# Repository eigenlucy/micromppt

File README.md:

# [micromppt](https://eigenlucy.github.io/projects/micromppt/)

SPV1040 Based 5W MPPT Boost Charger With Autonomous Perturb-and-Observe Set Point Adjustment

Tiny, versatile, high efficiency solar charging, designed with Meshtastic clients in mind

This release has been configured for single cell lipo charging, and includes an [XB3306](https://www.lcsc.com/datasheet/lcsc_datasheet_2106062206_XySemi-XB3306D_C2759992.pdf) lithium battery protection circuit. I have tested this converter with avariety of cell chemistries, as well as supercapacitors, and I will release a more minimal SPV1040 package in the upcoming week with configuration guidelines to for a more general purpose multichemistry solar charging module. [See the project page on my website for more configuration guidelines, panel recommendations, and ordering info (WIP)](https://eigenlucy.github.io/projects/micromppt/).

Built with atopile and KICAD 9. See my [atopile usage guide](/ATO_USAGE.md) for help installing and using atopile

TO DO:
- Split the project into a base micromppt module and a number of input and output projection modules
- Solve Vout divider with assertions, add cutoff and BPC for other chemistries

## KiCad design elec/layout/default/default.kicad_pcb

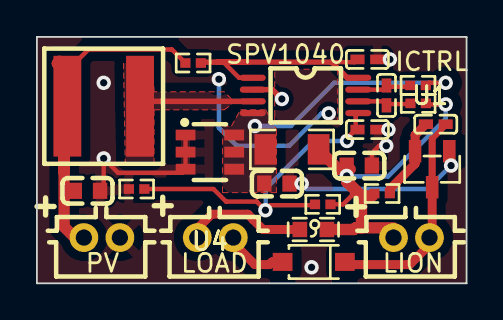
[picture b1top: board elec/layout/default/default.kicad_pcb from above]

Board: 2 copper layers, 23.9 x 13.7 mm, 23 parts (0 on the bottom side), 13 nets.

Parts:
C2: 4.7µF ±10% 16V X5R; C0603
C3: 10µF ±20% 6.3V X5R; C0603
C4: 100nF ±10% 16V X7R; C0402
C5: 1nF ±20% 50V X7R; C0402
C6: 1µF ±10% 25V X5R; C0402
D1: SOD-123F_L2.7-W1.6-LS3.8-RD-1
F1: F0603
R1: 1MΩ ±1% 62.5mW; R0402
R2: 390kΩ ±1% 62.5mW; R0402
R3, R4, R5: 1kΩ ±1% 62.5mW; R0402
R6: 10mΩ ±1% 1W; R1206
U1: TSSOP-8_L4.4-W3.0-P0.65-LS6.4-BL
U2: 100nF ±10% 16V X7R; C0402
U3: IND-SMD_L6.6-W6.4
U4: SOT-23-6_L2.9-W1.6-P0.95-LS2.8-BR
U5: 10µF ±20% 6.3V X5R; C0603
U6: 10kΩ ±1% 62.5mW; R0402
U7, U8, U10: CONN-TH_B2B-PH-K-S
U9: SOT-23-3_L2.9-W1.3-P1.90-LS2.4-BR

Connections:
ICTRL_MINUS: C6.2, R5.1, U1.6
ICTRL_PLUS: C6.1, R4.1, U1.7
LX: U1.3, U3.2
MPP_SET: C4.1, R3.2, U1.1, U1.8
VCTRL: C5.1, R1.2, R2.1, U1.5
VDD: U2.1, U6.1, U9.2
VOUT: C2.1, R4.2, R6.1, U1.4, U4.4, U4.5, U4.6
Vbat: C3.1, F1.1, R1.1, R5.2, R6.2, U6.2, U7.1
Vbatr-GND: D1.1, U2.2, U7.2, U9.3
Vpv: R3.1, U3.1, U5.1, U8.1
_1: F1.2, U10.1
anode: D1.2, U10.2
power_shim-GND: C2.2, C3.2, C4.2, C5.2, R2.2, U1.2, U4.1, U4.2, U4.3, U5.2, U8.2, U9.1

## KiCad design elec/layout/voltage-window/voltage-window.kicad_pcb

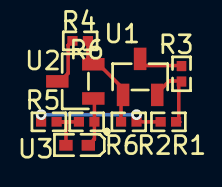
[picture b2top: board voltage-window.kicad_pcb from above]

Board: 2 copper layers, 9 parts (0 on the bottom side), 7 nets.

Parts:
R1, R2, R3, R4, R5, R6: 10kΩ ±1% 62.5mW; R0402-56259e
U1, U2: SOT-23-3_L2.9-W1.3-P1.90-LS2.4-BR-688f29
U3: LED0402-R-RD-049f90

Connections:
A: R3.2, U1.3
K: R2.2, R4.1, U1.1, U2.2
OUT: R6.2, U2.1, U3.2
REF: R1.2, R3.1, U1.2
anode: R5.2, R6.1, U3.1
gnd: R4.2, U2.3
hv: R1.1, R2.1, R5.1

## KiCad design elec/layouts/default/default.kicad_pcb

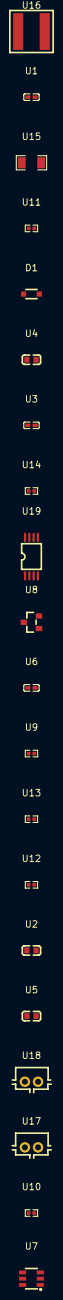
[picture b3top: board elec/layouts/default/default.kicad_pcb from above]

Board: 2 copper layers, 20 parts (0 on the bottom side), 11 nets, no tracks yet.

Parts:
D1: SOD-323F_L1.7-W1.3-LS2.5-R-RD
U1: 1µF ±10% 25V X5R; C0402-b3ef17
U2, U5: 10µF ±20% 6.3V X5R; C0603-bd72f6
U3: 100nF ±10% 16V X7R; C0402-b3ef17
U4: 4.7µF ±10% 10V X5R; C0603-bd72f6
U6: 1nF ±20% 50V X7R; C0402-b3ef17
U7: SOT-23-6_L2.9-W1.6-P0.95-LS2.8-BR
U8: SOT-23_L2.9-W1.3-P1.90-LS2.4-BR
U9: 1MΩ ±1% 62.5mW; R0402-56259e
U10: 330kΩ ±1% 62.5mW; R0402-56259e
U11, U13, U14: 1kΩ ±1% 62.5mW; R0402-56259e
U12: 10kΩ ±1% 62.5mW; R0402-56259e
U15: 10mΩ ±1% 1W; R1206-bdb864
U16: IND-SMD_L6.6-W6.4
U17, U18: CONN-TH_B2B-PH-K-S
U19: TSSOP-8_L4.4-W3.0-P0.65-LS6.4-BL

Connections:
D: D1.1, U8.3, U18.1
G: D1.2, U8.1, U12.1
ICTRL_MINUS: U1.2, U14.1, U19.6
ICTRL_PLUS: U1.1, U13.1, U19.7
LX: U16.2, U19.3
S: U2.1, U8.2, U11.1, U16.1
VCTRL: U6.1, U9.2, U10.1, U19.5
VOUT: U4.1, U13.2, U15.1, U19.4
XSHUT: U3.1, U11.2, U19.1, U19.8
gnd: U2.2, U3.2, U4.2, U5.2, U6.2, U10.2, U12.2, U17.2, U18.2, U19.2
hv: U5.1, U9.1, U14.2, U15.2, U17.1

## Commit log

2024-11-28 unfinished
2024-11-28 testing
2024-11-28 built
2024-11-28 started layout
2024-11-29 finishing netlist
2024-11-29 pcb v1
2024-11-29 double squiggle
2024-12-05 pcb update and actions retry
2024-12-05 fixed build errors
2024-12-08 removed extra build folders
2025-01-10 connected c3/r1
2025-02-06 fixed unconnected vout feedback pin
2025-02-06 MICROMPPT V2
2025-02-06 built with ato v3, MICROMPPT V2 order
2025-02-08 v3 update
2025-03-08 Revert "v3 update"
    This reverts commit 3d2f1a32cb7bdd8d1440f52d8c2b71f7bcce05a5.
2025-03-08 fixed :woozy:
2025-03-08 fixed
2025-03-09 Micromppt V3 (fr this time)
2025-03-09 Micromppt V3 (fr this time) x2
2025-03-10 Micromppt V3 added githash
2025-03-10 new connector
2025-04-08 micromppt V3
2025-04-09 built with ato V3!
2025-04-09 fixed .github/workflows/ci.yml and set github actions versions to v4
2025-04-13 readme
2025-04-13 removed image
2025-04-15 init
2025-04-15 compiled with v4
2025-04-15 laptop backup
2025-04-16 changed layouts to original layout folder name, fixed layout syncing
2025-04-16 added voltage window monitor
2025-04-19 ready for publishing on the ato repo
2025-04-19 added package stuff to ato.yaml
2025-04-22 added load output and BPC
2025-04-22 reran DRC
2025-04-22 changed Vout set to 4.2
2025-04-22 added load PTC, fixed githash
2025-04-22 fixed readme
2025-04-22 rebuilt, added picture to readme, ato usage guidelines
2025-04-22 added graphics
2025-08-28 building with 0.11.6
2025-08-28 updated files, layout looked unaltered
2025-09-06 update! works with current ato version
2025-09-06 update! works with current ato version. reran DRC
